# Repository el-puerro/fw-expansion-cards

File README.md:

# 3rd party open hardware Expansion cards, compatible with Framework machines

This repository contains all the design files, gerbers, BOMS, and (if applicable)
code for my Framework-compatible 3rd-party expansion cards

Everything is licensed as CC BY 4.0, just like Frameworks original design files,
which you can find [here](https://github.com/FrameworkComputer/ExpansionCards/tree/main)

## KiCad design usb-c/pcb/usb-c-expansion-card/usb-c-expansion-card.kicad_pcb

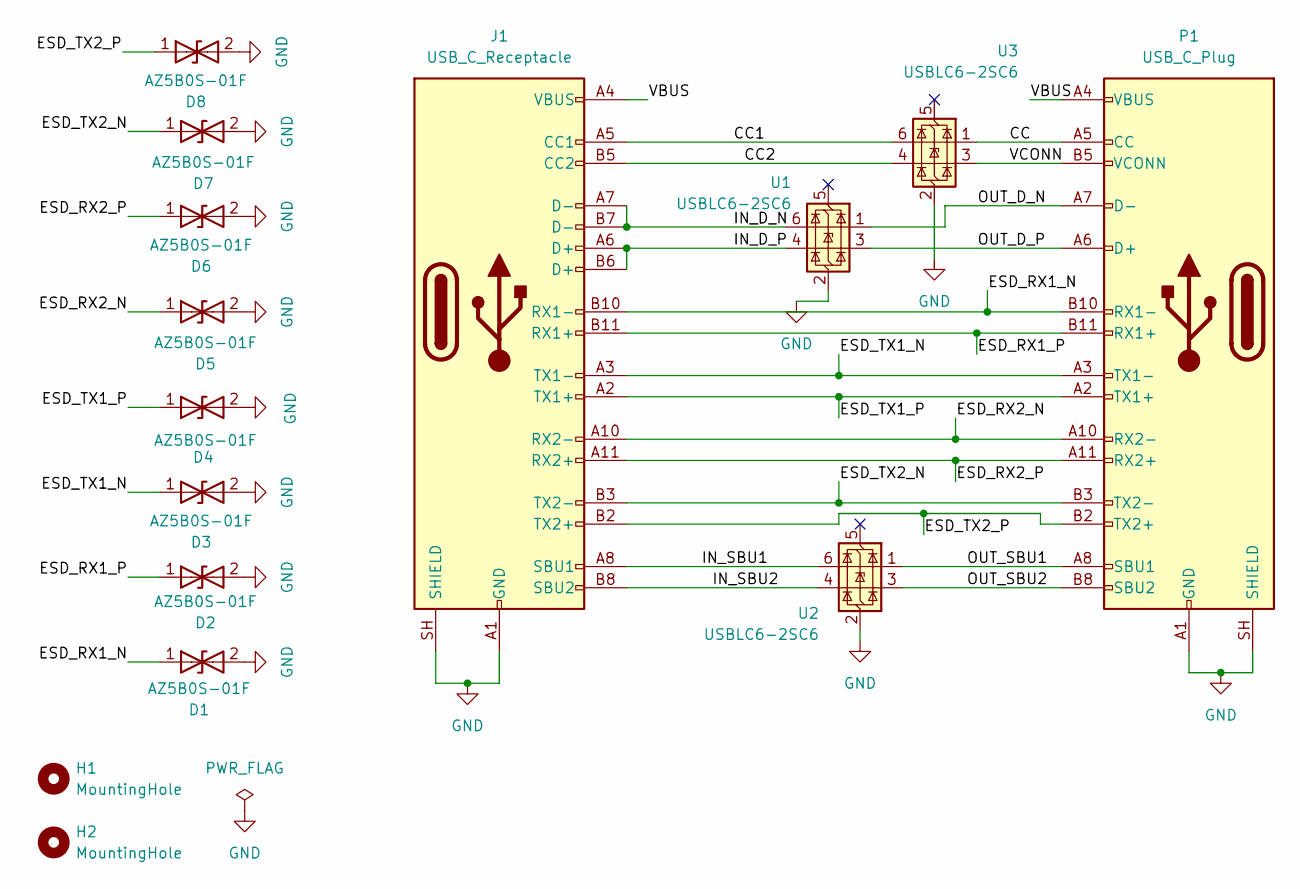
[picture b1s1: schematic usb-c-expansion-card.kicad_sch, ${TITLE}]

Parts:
D1, D2, D3, D4, D5, D6, D7, D8: AZ5B0S-01F; D_0603_1608Metric
H1, H2: MountingHole; MountingHole_2.2mm_M2_DIN965_Pad
J1: USB_C_Receptacle; AMPHENOL_12402075E512A
P1: USB_C_Plug; USB_C_Plug_Molex_105444
U1, U2, U3: USBLC6-2SC6; SOT-23-6

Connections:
/CC: P1.A5 (CC), U3.1 (I/O1)
/CC1: J1.A5 (CC1), U3.6 (I/O1)
/CC2: J1.B5 (CC2), U3.4 (I/O2)
/ESD_RX1_N: D1.1 (A1), J1.B10 (RX1-), P1.B10 (RX1-)
/ESD_RX1_P: D2.1 (A1), J1.B11 (RX1+), P1.B11 (RX1+)
/ESD_RX2_N: D5.1 (A1), J1.A10 (RX2-), P1.A10 (RX2-)
/ESD_RX2_P: D6.1 (A1), J1.A11 (RX2+), P1.A11 (RX2+)
/ESD_TX1_N: D3.1 (A1), J1.A3 (TX1-), P1.A3 (TX1-)
/ESD_TX1_P: D4.1 (A1), J1.A2 (TX1+), P1.A2 (TX1+)
/ESD_TX2_N: D7.1 (A1), J1.B3 (TX2-), P1.B3 (TX2-)
/ESD_TX2_P: D8.1 (A1), J1.B2 (TX2+), P1.B2 (TX2+)
/IN_D_N: J1.A7 (D-), J1.B7 (D-), U1.6 (I/O1)
/IN_D_P: J1.A6 (D+), J1.B6 (D+), U1.4 (I/O2)
/IN_SBU1: J1.A8 (SBU1), U2.6 (I/O1)
/IN_SBU2: J1.B8 (SBU2), U2.4 (I/O2)
/OUT_D_N: P1.A7 (D-), U1.1 (I/O1)
/OUT_D_P: P1.A6 (D+), U1.3 (I/O2)
/OUT_SBU1: P1.A8 (SBU1), U2.1 (I/O1)
/OUT_SBU2: P1.B8 (SBU2), U2.3 (I/O2)
/VBUS: J1.A4 (VBUS), J1.A9 (VBUS), J1.B4 (VBUS), J1.B9 (VBUS), P1.A4 (VBUS), P1.A9 (VBUS), P1.B4 (VBUS), P1.B9 (VBUS)
/VCONN: P1.B5 (VCONN), U3.3 (I/O2)
GND: D1.2 (A2), D2.2 (A2), D3.2 (A2), D4.2 (A2), D5.2 (A2), D6.2 (A2), D7.2 (A2), D8.2 (A2), J1.A1 (GND), J1.A12 (GND), J1.B1 (GND), J1.B12 (GND), J1.SH (SHIELD), P1.A1 (GND), P1.A12 (GND), P1.B1 (GND), P1.B12 (GND), P1.SH (SHIELD), U1.2 (GND), U2.2 (GND), U3.2 (GND)

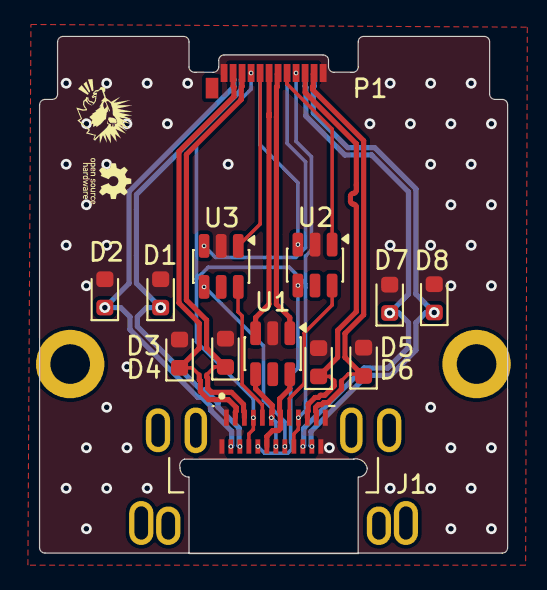
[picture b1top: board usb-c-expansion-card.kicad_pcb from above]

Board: 4 copper layers, 26.0 x 28.7 mm, 15 parts (0 on the bottom side), 22 nets.

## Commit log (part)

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2023-02-08 first testfit

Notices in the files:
parts and their libraries:
Licensed under CC BY 4.0 by Framework Computer Inc.
